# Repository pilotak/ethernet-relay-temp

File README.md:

# STM32F103C8 (BluePill) based temperature node with relay

## Features
- variable power supply: 5-15V (depends on relay coil)
- 1-wire bus for DS18B20 temperature sensors
- 1x thermistor input
- 1x SPST relay with ARC suppression
- controlled over MQTT

## MQTT topics
- `nameOfBoard/dtemp/*` = dallas temperature *(aterisk is temp address)*
- `nameOfBoard/atemp/*` = thermistor temperature *(aterisk is analog temp index)*
- `nameOfBoard/status` = online status
- `nameOfBoard/err` = dallas error, tells you index of the bad sensor
- `nameOfBoard/count` = number of dallas sensors found
- `nameOfBoard/relay/0` = state of relay
- `nameOfBoard/relay/0/set` = command for relay, can be either `0` or `1`

## BOM
| Qty | Component | Value | Package |
|:---:| --------- | ----- | ------- |
| 1 | Ceramic capacitor | 10uF | C0805 |
| 1 | Electrolytic capacitor | 100uF | E2-5 |
| 1 | Polypropylene capacitor | R463I24705001K | C150-084X183 |
| 1 | Diode | S1B |DO214AC (SMA) |
| 1 | Shottky diode | SS16 | DO214AC (SMA) |
| 1 | Barrel jack | 2.1mm | |
| 1 | Relay | RM85-2021-35-1005 | |
| 1 | NPN transistor | BC817 | SOT23-BEC |
| 1 | Resistor | 1K | R0805 |
| 1 | Resistor | 4K7 | R0805 |
| 1 | Resistor | 10K | R0805 |
| 1 | Resistor | 160R | R2010 |
| 1 | Ethernet module | ENC28J60 | |
| 1 | LDO regulator | LM1117-3.3 | SOT223 |
| 1 | Processor module | STM32F103C8T6 | |
| 2 | Terminal | Wago 236-740-5,08 | |
| 1 | Terminal | KF350-3.50-2P | |
| 3 | Terminal | KF350-3.50-3P | |
| 1 | Case | KRADEX Z76 | |

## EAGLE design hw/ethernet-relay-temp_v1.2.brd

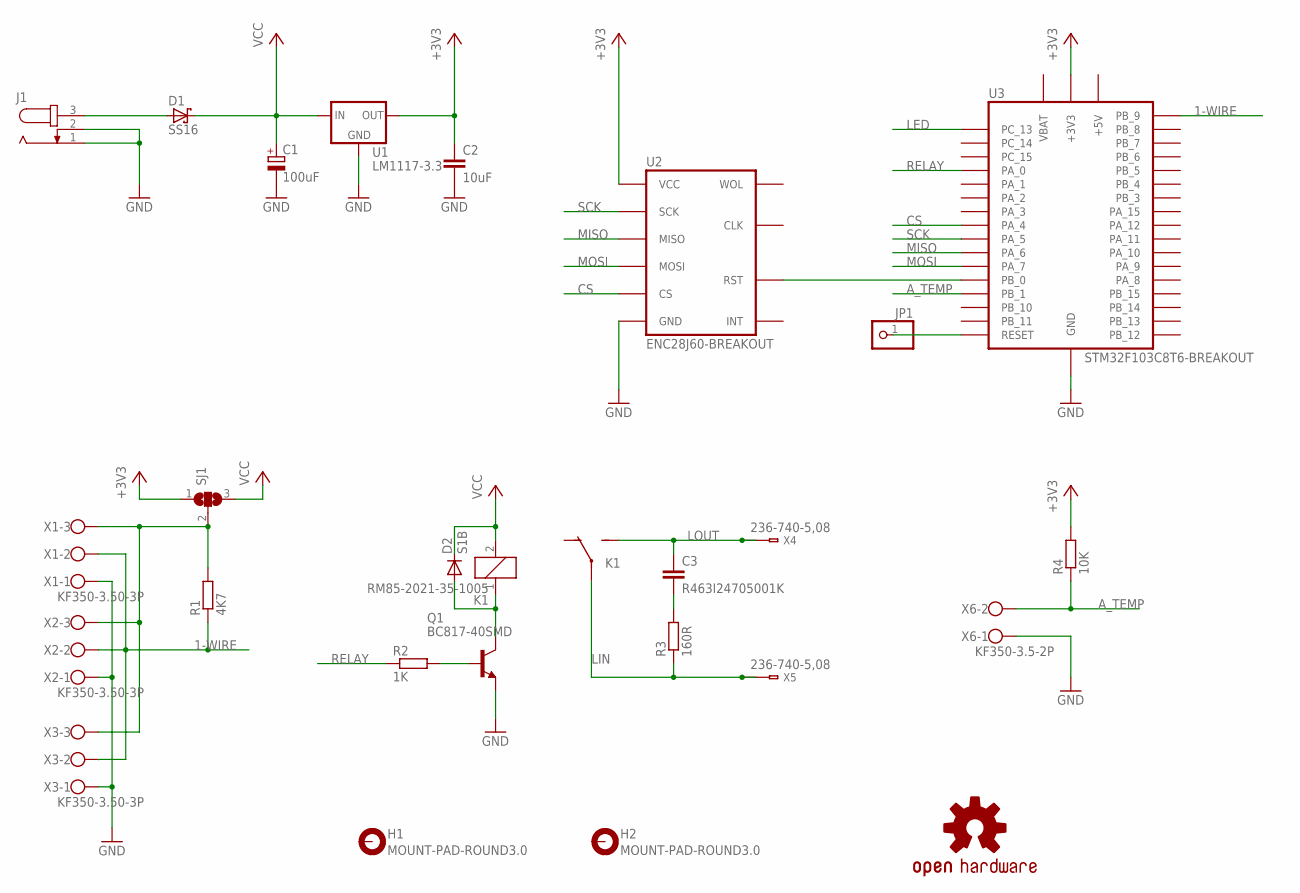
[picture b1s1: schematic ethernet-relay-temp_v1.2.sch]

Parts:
C1: 100uF; E2-5
C2: 10uF; C0805
C3: R463I24705001K; C150-084X183
D1: SS16; DO214AC
D2: S1B; DO214AC
H1, H2: MOUNT-PAD-ROUND3.0; 3,0-PAD
J1: JACK-PLUG0; SPC4077
JP1: PINHD-1X1; 1X01
K1: RM85-2021-35-1005; RM85
LOGO1: OSHW-LOGOS-COPPER; OSHW-LOGO-S_COPPER
Q1: BC817-40SMD; SOT23-BEC
R1: 4K7; R0805
R2: 1K; R0805
R3: 160R; R2010
R4: 10K; R0805
SJ1: SJ2W; SJ_2
U1: LM1117-3.3; SOT223
U2: ENC28J60-BREAKOUT; ENC28J60
U3: STM32F103C8T6-BREAKOUT; STM32F103C8T6
X1, X2, X3: KF350-3.50-3P
X4, X5: 236-740-5,08; 236-4XX
X6: KF350-3.5-2P; KF350-3.50-2P

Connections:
1-WIRE: R1.1, U3.PB_9, X1.2, X2.2, X3.2
+3V3: C2.1, R4.2, SJ1.1, U1.2 (OUT), U1.4 (OUT), U2.VCC, U3.+3V3, U3.+3V3@1 (+3V3)
+5V: U3.+5V
A_TEMP: R4.1, U3.PB_1, X6.2
CS: U2.CS, U3.PA_4
GND: C1.-, C2.2, J1.1, J1.2, Q1.E, U1.1 (GND), U2.GND, U3.GND, U3.GND@1 (GND), U3.GND@2 (GND), X1.1, X2.1, X3.1, X6.1
LED: U3.PC_13
LIN: K1.11, K1.21, R3.1, X5.1@1 (A1), X5.1@2 (B1)
LOUT: C3.1, K1.14 (NO), K1.24 (NO), X4.1@1 (A1), X4.1@2 (B1)
MISO: U2.SO (MISO), U3.PA_6
MOSI: U2.SI (MOSI), U3.PA_7
unnamed: JP1.1, U3.RESET
unnamed: U2.RST, U3.PB_0
unnamed: C3.2, R3.2
unnamed: D2.A, K1.1, Q1.C
unnamed: Q1.B, R2.2
unnamed: R1.2, SJ1.2, X1.3, X2.3, X3.3
unnamed: D1.A, J1.3
RELAY: R2.1, U3.PA_0
SCK: U2.SCK, U3.PA_5
VBAT: U3.VBAT
VCC: C1.+, D1.C, D2.C, K1.2, SJ1.3, U1.3 (IN)

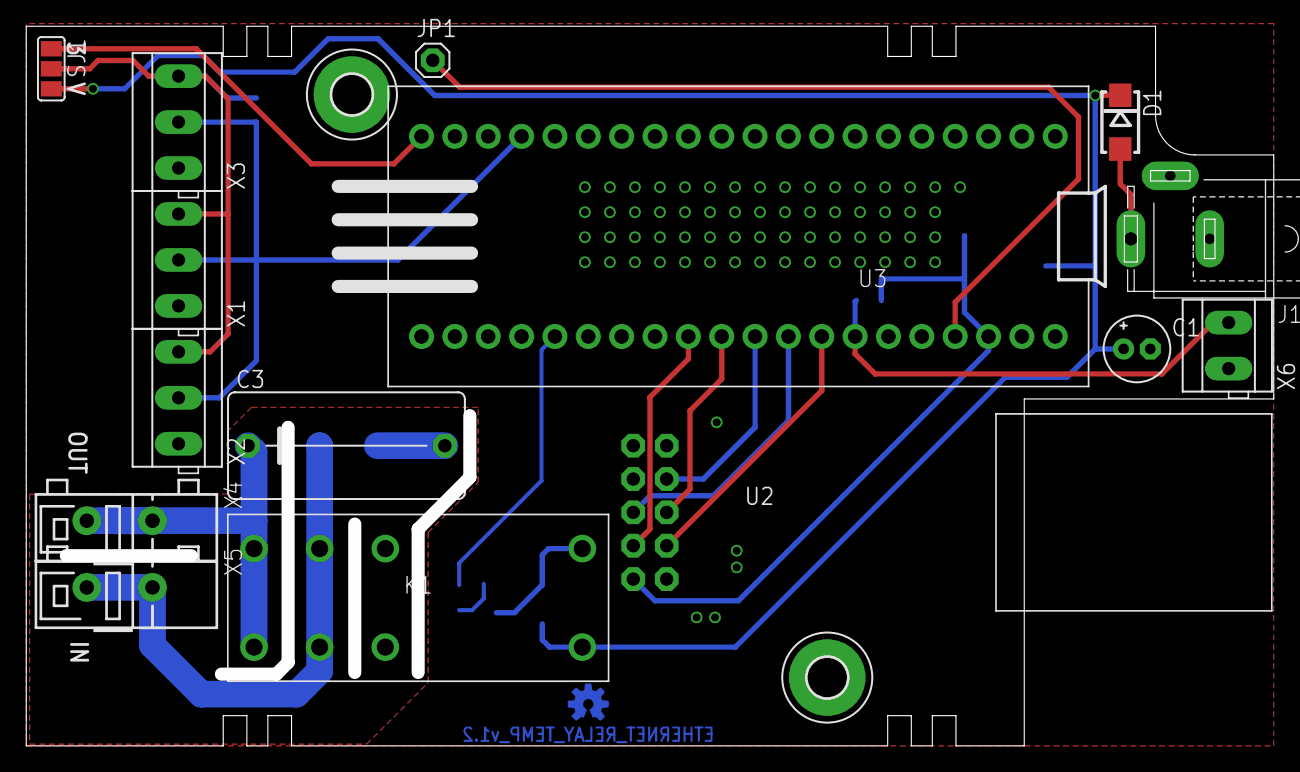
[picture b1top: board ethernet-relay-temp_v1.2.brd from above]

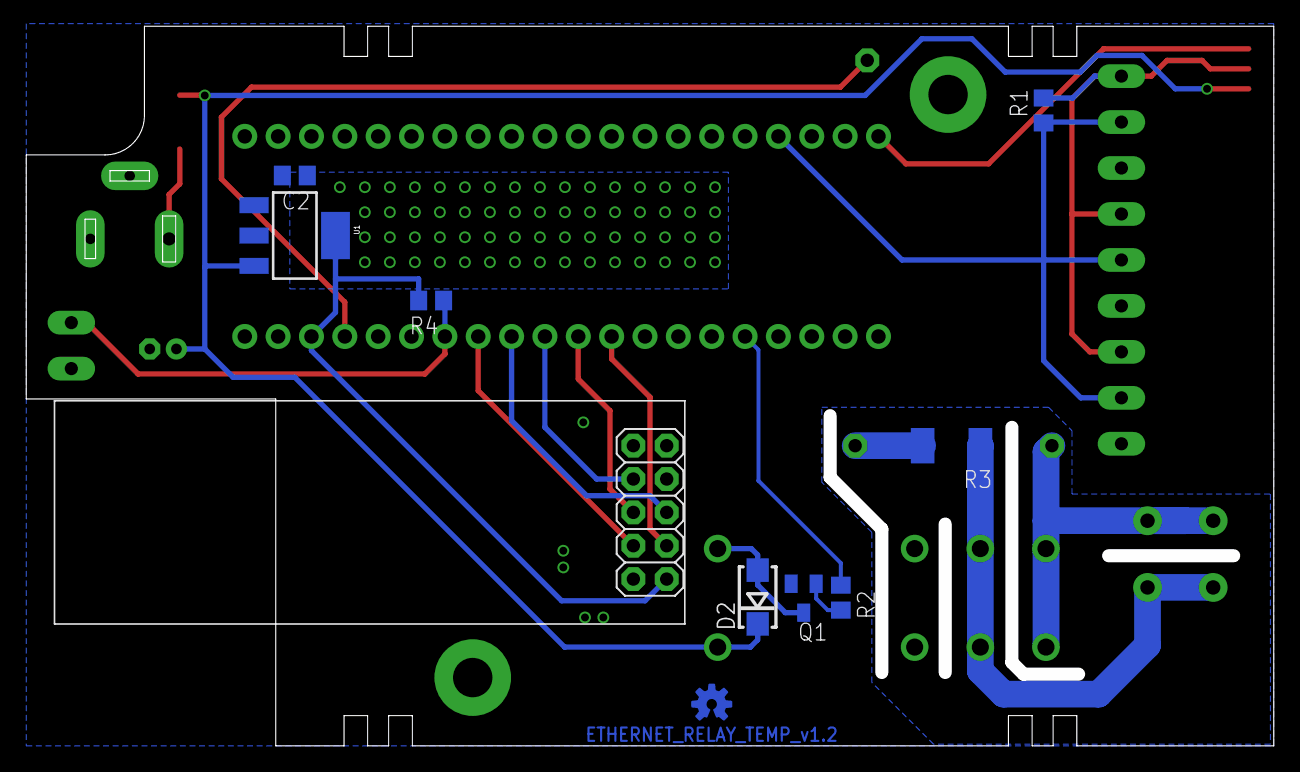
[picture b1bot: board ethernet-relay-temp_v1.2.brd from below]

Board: 2 copper layers, 94.0 x 53.8 mm, 26 parts (9 on the bottom side), 19 nets.

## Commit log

2018-11-18 init
2018-12-02 rename + count topic
2018-12-02 travis
2018-12-02 BOM update
    [ci skip]
2018-12-02 pin change
2018-12-02 readme update
    [ci skip]
2018-12-04 pic
    [ci skip]
2018-12-08 longer watchdog + temp string fix
2018-12-08 macro fix
2018-12-27 mqtt restart
2018-12-27 wdt + reset update
2018-12-27 12bit ADC as default
2018-12-27 snprintf to dtostr + fixes
2019-01-03 compatibility with new/old STM32 core
2019-01-03 settings example
2019-01-03 debug fix
2020-05-28 fix adc warning
2020-08-16 folder restructure
2020-08-16 moved from Travis to GithubCI
2020-08-16 CI build debug as well
2020-08-16 CI update
2020-09-24 CI split build & release
2020-09-24 CI correct naming

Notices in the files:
parts and their libraries:
SparkFun-Aesthetics: Licensing: Creative Commons ShareAlike 4.0 International - https://creativecommons.org/licenses/by-sa/4.0
